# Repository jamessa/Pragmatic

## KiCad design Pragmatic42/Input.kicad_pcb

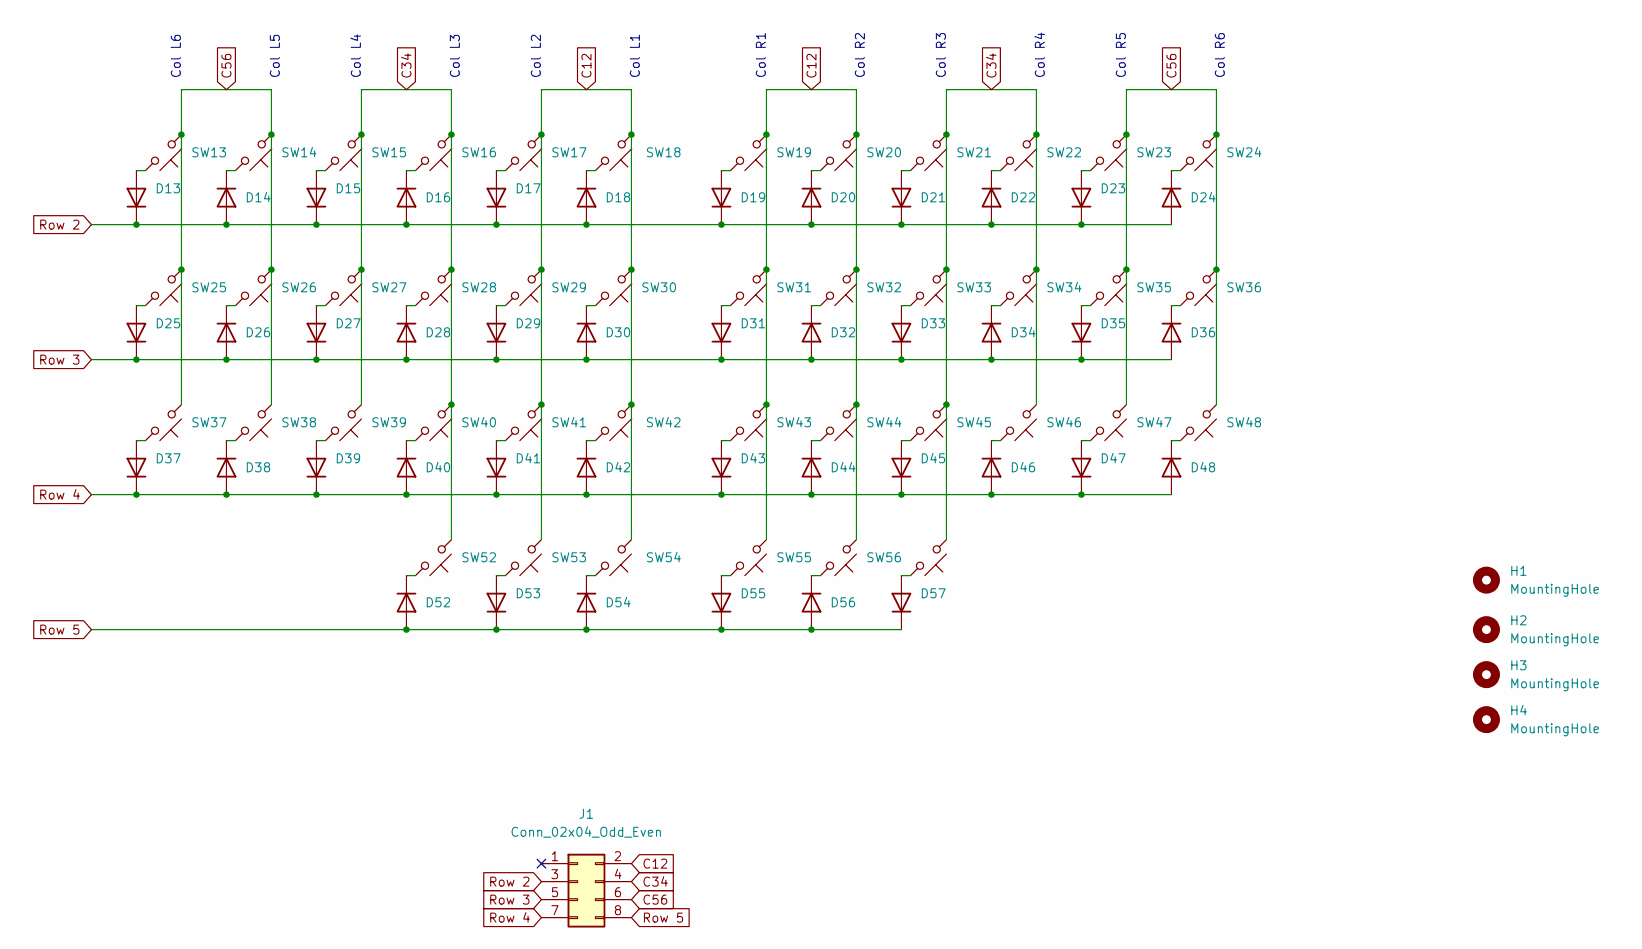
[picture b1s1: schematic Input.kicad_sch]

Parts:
D13, D14, D15, D16, D17, D18, D19, D20, D21, D22, D23, D24, D25, D26, D27, D28, D29, D30, D31, D32, D33, D34, D35, D36, D37, D38, D39, D40, D41, D42, D43, D44, D45, D46, D47, D48, D52, D53, D54, D55, D56, D57: 1N4448W; D3_SMD_v2
H1, H2, H3, H4: MountingHole; MountingHole_3.2mm_M3_DIN965
J1: Conn_02x04_Odd_Even; matrix_connector
SW13, SW14, SW15, SW16, SW17, SW18, SW25, SW26, SW27, SW28, SW29, SW30, SW37, SW38, SW39, SW40, SW41, SW42, SW52, SW53, SW54: SW_Push_45deg; ChocV1_Hotswap_reverse
SW19, SW20, SW21, SW22, SW23, SW24, SW31, SW32, SW33, SW34, SW35, SW36, SW43, SW44, SW45, SW46, SW47, SW48, SW55, SW56, SW57: SW_Push_45deg; ChocV1_Hotswap

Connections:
C12: J1.2, SW17.1, SW18.1, SW19.1, SW20.1, SW29.1, SW30.1, SW31.1, SW32.1, SW41.1, SW42.1, SW43.1, SW44.1, SW53.1, SW54.1, SW55.1, SW56.1
C34: J1.4, SW15.1, SW16.1, SW21.1, SW22.1, SW27.1, SW28.1, SW33.1, SW34.1, SW39.1, SW40.1, SW45.1, SW46.1, SW52.1, SW57.1
C56: J1.6, SW13.1, SW14.1, SW23.1, SW24.1, SW25.1, SW26.1, SW35.1, SW36.1, SW37.1, SW38.1, SW47.1, SW48.1
unnamed: D13.2 (A), SW13.2
unnamed: D14.1 (K), SW14.2
unnamed: D15.2 (A), SW15.2
unnamed: D16.1 (K), SW16.2
unnamed: D17.2 (A), SW17.2
unnamed: D18.1 (K), SW18.2
unnamed: D19.2 (A), SW19.2
unnamed: D20.1 (K), SW20.2
unnamed: D21.2 (A), SW21.2
unnamed: D22.1 (K), SW22.2
unnamed: D23.2 (A), SW23.2
unnamed: D24.1 (K), SW24.2
unnamed: D25.2 (A), SW25.2
unnamed: D26.1 (K), SW26.2
unnamed: D27.2 (A), SW27.2
unnamed: D28.1 (K), SW28.2
unnamed: D29.2 (A), SW29.2
unnamed: D30.1 (K), SW30.2
unnamed: D31.2 (A), SW31.2
unnamed: D32.1 (K), SW32.2
unnamed: D33.2 (A), SW33.2
unnamed: D34.1 (K), SW34.2
unnamed: D35.2 (A), SW35.2
unnamed: D36.1 (K), SW36.2
unnamed: D37.2 (A), SW37.2
unnamed: D38.1 (K), SW38.2
unnamed: D39.2 (A), SW39.2
unnamed: D40.1 (K), SW40.2
unnamed: D41.2 (A), SW41.2
unnamed: D42.1 (K), SW42.2
unnamed: D43.2 (A), SW43.2
unnamed: D44.1 (K), SW44.2
unnamed: D45.2 (A), SW45.2
unnamed: D46.1 (K), SW46.2
unnamed: D47.2 (A), SW47.2
unnamed: D48.1 (K), SW48.2
unnamed: D52.1 (K), SW52.2
unnamed: D53.2 (A), SW53.2
unnamed: D54.1 (K), SW54.2
unnamed: D55.2 (A), SW55.2
unnamed: D56.1 (K), SW56.2
unnamed: D57.2 (A), SW57.2
Row 2: D13.1 (K), D14.2 (A), D15.1 (K), D16.2 (A), D17.1 (K), D18.2 (A), D19.1 (K), D20.2 (A), D21.1 (K), D22.2 (A), D23.1 (K), D24.2 (A), J1.3
Row 3: D25.1 (K), D26.2 (A), D27.1 (K), D28.2 (A), D29.1 (K), D30.2 (A), D31.1 (K), D32.2 (A), D33.1 (K), D34.2 (A), D35.1 (K), D36.2 (A), J1.5
Row 4: D37.1 (K), D38.2 (A), D39.1 (K), D40.2 (A), D41.1 (K), D42.2 (A), D43.1 (K), D44.2 (A), D45.1 (K), D46.2 (A), D47.1 (K), D48.2 (A), J1.7
Row 5: D52.2 (A), D53.1 (K), D54.2 (A), D55.1 (K), D56.2 (A), D57.1 (K), J1.8

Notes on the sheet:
Col L4
Col R1
Col L1
Col R5
Col L6
Col R3
Col L3
Col R6
Col L5
Col R2
Col R4
Col L2

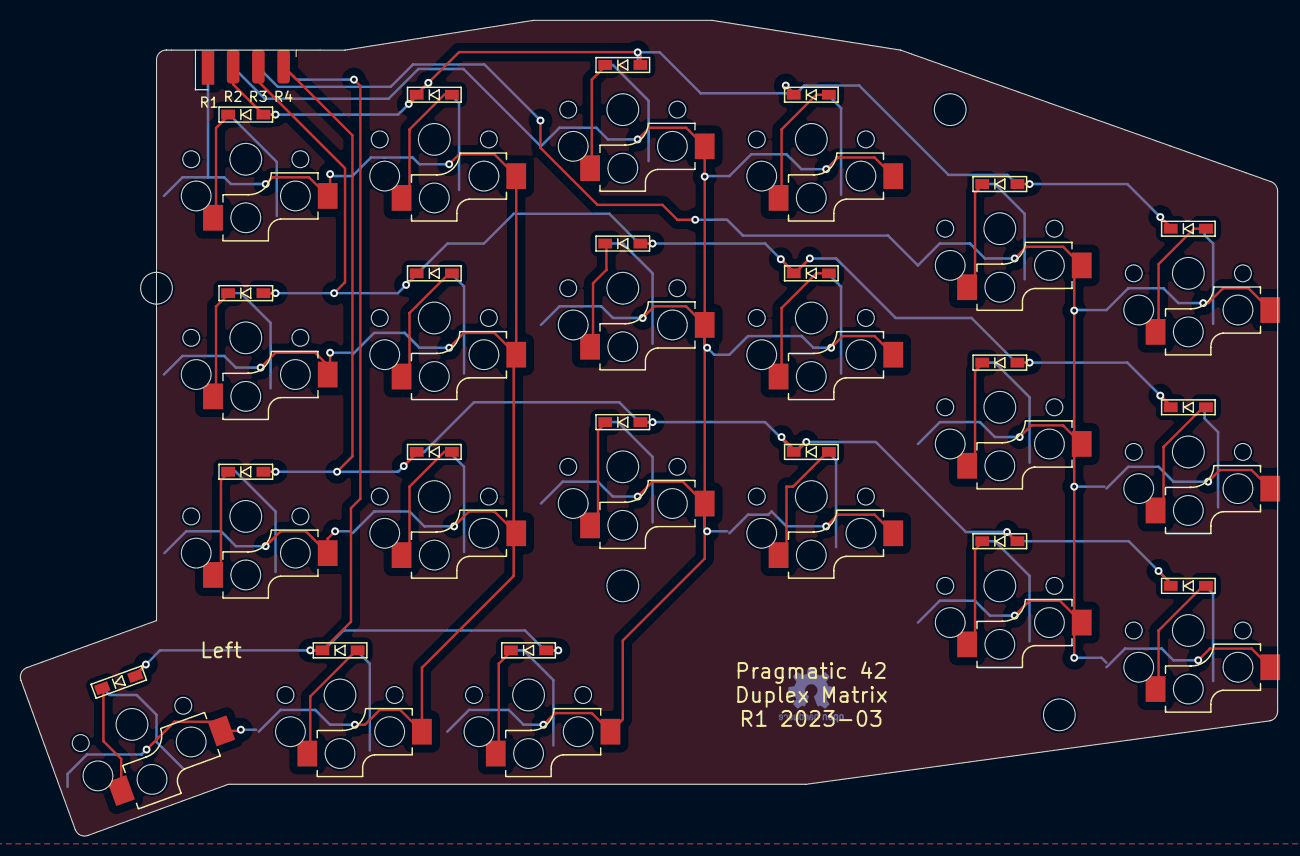
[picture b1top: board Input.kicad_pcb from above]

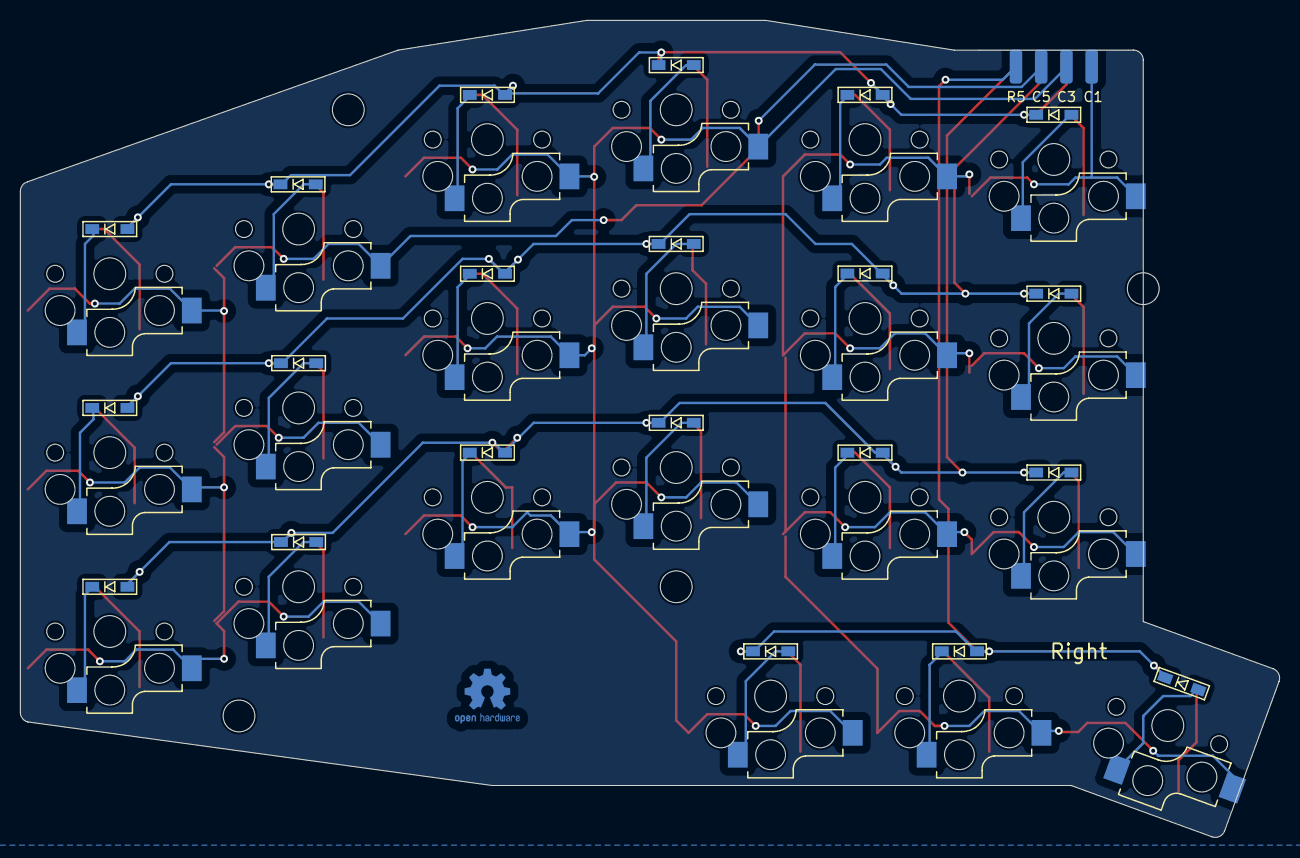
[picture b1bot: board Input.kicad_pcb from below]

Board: 2 copper layers, 126.7 x 82.2 mm, 89 parts (42 on the bottom side), 49 nets.

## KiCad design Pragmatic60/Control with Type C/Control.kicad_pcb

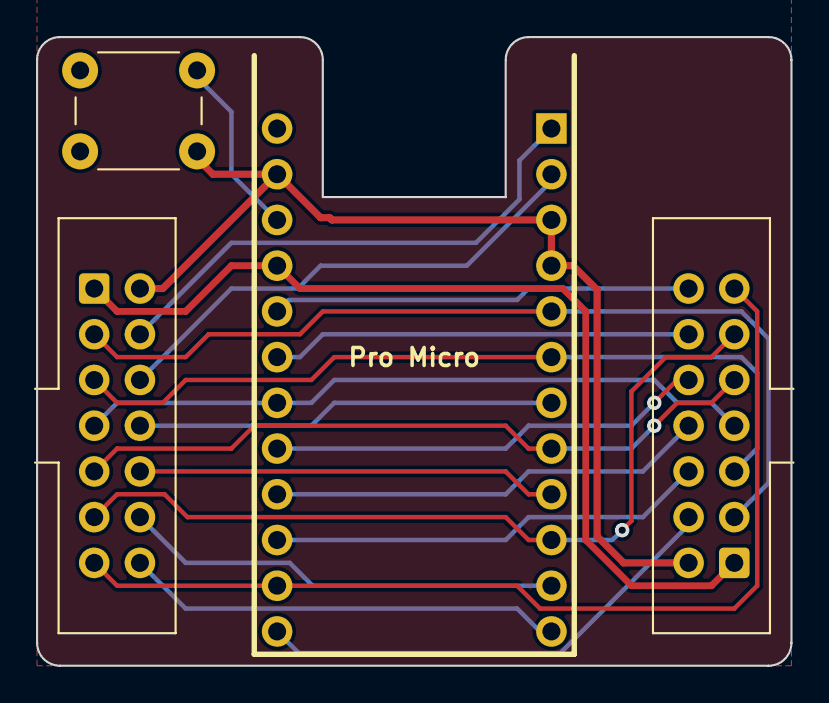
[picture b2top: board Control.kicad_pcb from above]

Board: 2 copper layers, 41.9 x 34.9 mm, 6 parts (1 on the bottom side), 21 nets.

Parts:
J1: L; IDC-Header_2x07_P2.54mm_Vertical
J2: R; IDC-Header_2x07_P2.54mm_Vertical
L1: JLC Legend
Logo1: OSHW-Symbol_6.7x6mm_Copper
SW1: SW_Push; SW_PUSH_6mm
U1: ProMicro; ProMicro Type C Reversed

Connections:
Col1: J1.4, U1.1 (TX0/PD3)
Col2: J1.6, U1.2 (RX1/PD2)
Col3: J1.8, U1.7 (4/PD4)
Col4: J1.10, U1.9 (6/PD7)
Col5: J1.12, U1.11 (8/PB4)
Col6: J1.14, U1.12 (9/PB5)
Col7: J2.4, U1.13 (10/PB6)
Col8: J2.6, U1.15 (14/PB3)
Col9: J2.8, U1.16 (15/PB1)
Col10: J2.10, U1.17 (A0/PF7)
Col11: J2.12, U1.19 (A2/PF5)
Col12: J2.14, U1.20 (A3/PF4)
GND: J1.2, J2.2, SW1.2, U1.3 (GND), U1.4 (GND), U1.23 (GND)
Reset: SW1.1, U1.22 (RST)
Row1: J1.3, J2.3, U1.5 (2/PD1)
Row2: J1.5, J2.5, U1.6 (3/PD0)
Row3: J1.7, J2.7, U1.18 (A1/PF6)
Row4: J1.9, J2.9, U1.8 (5/PC6)
Row5: J1.11, J2.11, U1.10 (7/PE6)
Row6: J1.13, J2.13, U1.14 (16/PB2)
VCC: J1.1, J2.1, U1.21 (VCC)

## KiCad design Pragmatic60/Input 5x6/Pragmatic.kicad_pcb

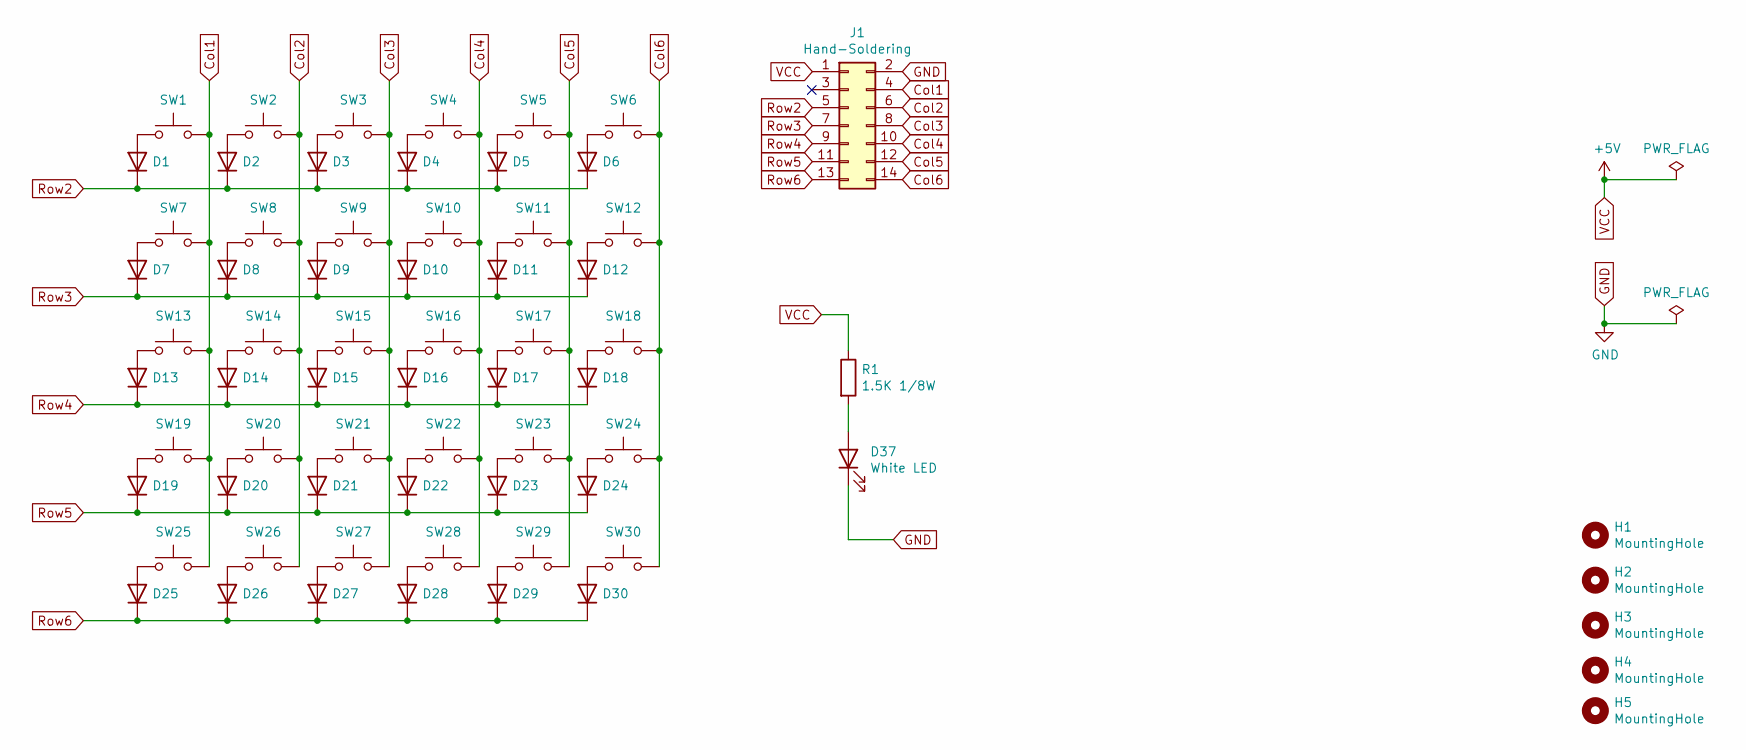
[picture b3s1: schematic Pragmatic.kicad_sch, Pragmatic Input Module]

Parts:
D1, D2, D3, D4, D5, D6, D7, D8, D9, D10, D11, D12, D13, D14, D15, D16, D17, D18, D19, D20, D21, D22, D23, D24, D25, D26, D27, D28, D29, D30: 1N4148; D3_SMD_v2; LCSC C81598
D37: White LED; LED_0805_2012Metric_Pad1.15x1.40mm_HandSolder; LCSC C434434
H1, H2, H3, H4, H5: MountingHole; MountingHole_2.5mm
J1: Hand-Soldering; IDC-Header_2x07_P2.54mm_Vertical; LCSC C3406
R1: 1.5K 1/8W; R_0805_2012Metric_Pad1.20x1.40mm_HandSolder; LCSC C4310
SW1, SW2, SW3, SW4, SW5, SW6, SW7, SW8, SW9, SW10, SW11, SW12, SW13, SW14, SW15, SW16, SW17, SW18, SW19, SW20, SW21, SW22, SW23, SW24, SW25, SW26, SW27, SW28, SW29, SW30: SW_Push; MX_Hotswap_MX_Choc_Solder; LCSC C2803348

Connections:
Col1: J1.4, SW1.2, SW7.2, SW13.2, SW19.2, SW25.2
Col2: J1.6, SW2.2, SW8.2, SW14.2, SW20.2, SW26.2
Col3: J1.8, SW3.2, SW9.2, SW15.2, SW21.2, SW27.2
Col4: J1.10, SW4.2, SW10.2, SW16.2, SW22.2, SW28.2
Col5: J1.12, SW5.2, SW11.2, SW17.2, SW23.2, SW29.2
Col6: J1.14, SW6.2, SW12.2, SW18.2, SW24.2, SW30.2
GND: D37.1 (K), J1.2
unnamed: D1.2 (A), SW1.1
unnamed: D2.2 (A), SW2.1
unnamed: D3.2 (A), SW3.1
unnamed: D4.2 (A), SW4.1
unnamed: D5.2 (A), SW5.1
unnamed: D6.2 (A), SW6.1
unnamed: D7.2 (A), SW7.1
unnamed: D8.2 (A), SW8.1
unnamed: D9.2 (A), SW9.1
unnamed: D10.2 (A), SW10.1
unnamed: D11.2 (A), SW11.1
unnamed: D12.2 (A), SW12.1
unnamed: D13.2 (A), SW13.1
unnamed: D14.2 (A), SW14.1
unnamed: D15.2 (A), SW15.1
unnamed: D16.2 (A), SW16.1
unnamed: D17.2 (A), SW17.1
unnamed: D18.2 (A), SW18.1
unnamed: D19.2 (A), SW19.1
unnamed: D20.2 (A), SW20.1
unnamed: D21.2 (A), SW21.1
unnamed: D22.2 (A), SW22.1
unnamed: D23.2 (A), SW23.1
unnamed: D24.2 (A), SW24.1
unnamed: D25.2 (A), SW25.1
unnamed: D26.2 (A), SW26.1
unnamed: D27.2 (A), SW27.1
unnamed: D28.2 (A), SW28.1
unnamed: D29.2 (A), SW29.1
unnamed: D30.2 (A), SW30.1
unnamed: D37.2 (A), R1.2
Row2: D1.1 (K), D2.1 (K), D3.1 (K), D4.1 (K), D5.1 (K), D6.1 (K), J1.5
Row3: D7.1 (K), D8.1 (K), D9.1 (K), D10.1 (K), D11.1 (K), D12.1 (K), J1.7
Row4: D13.1 (K), D14.1 (K), D15.1 (K), D16.1 (K), D17.1 (K), D18.1 (K), J1.9
Row5: D19.1 (K), D20.1 (K), D21.1 (K), D22.1 (K), D23.1 (K), D24.1 (K), J1.11
Row6: D25.1 (K), D26.1 (K), D27.1 (K), D28.1 (K), D29.1 (K), D30.1 (K), J1.13
VCC: J1.1, R1.1

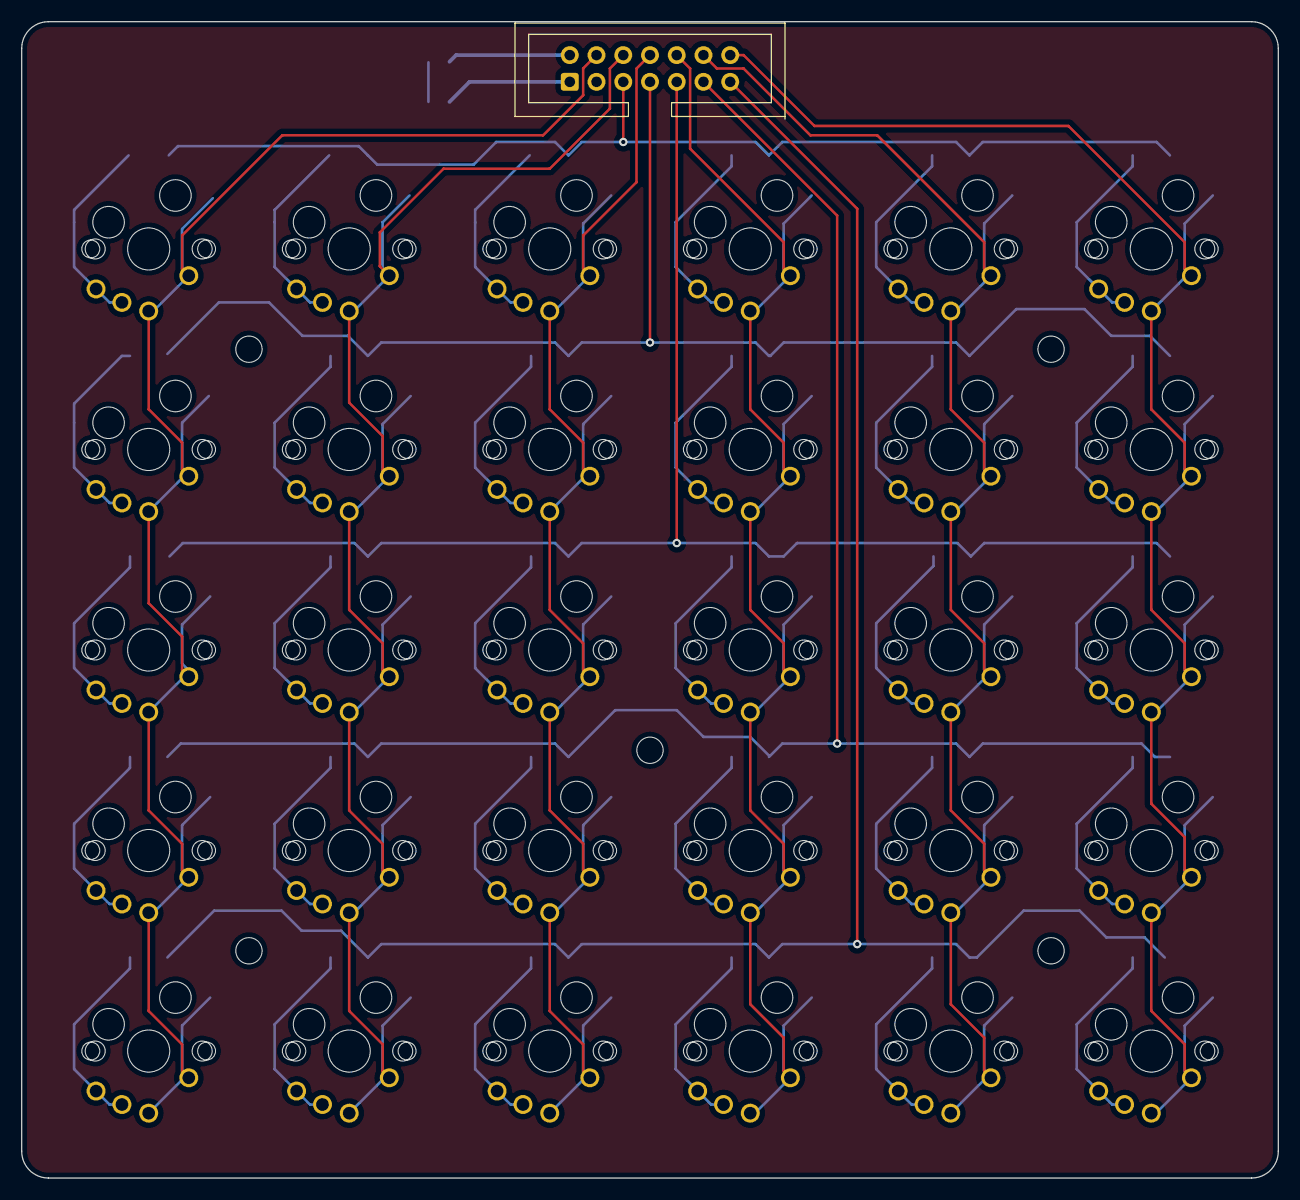
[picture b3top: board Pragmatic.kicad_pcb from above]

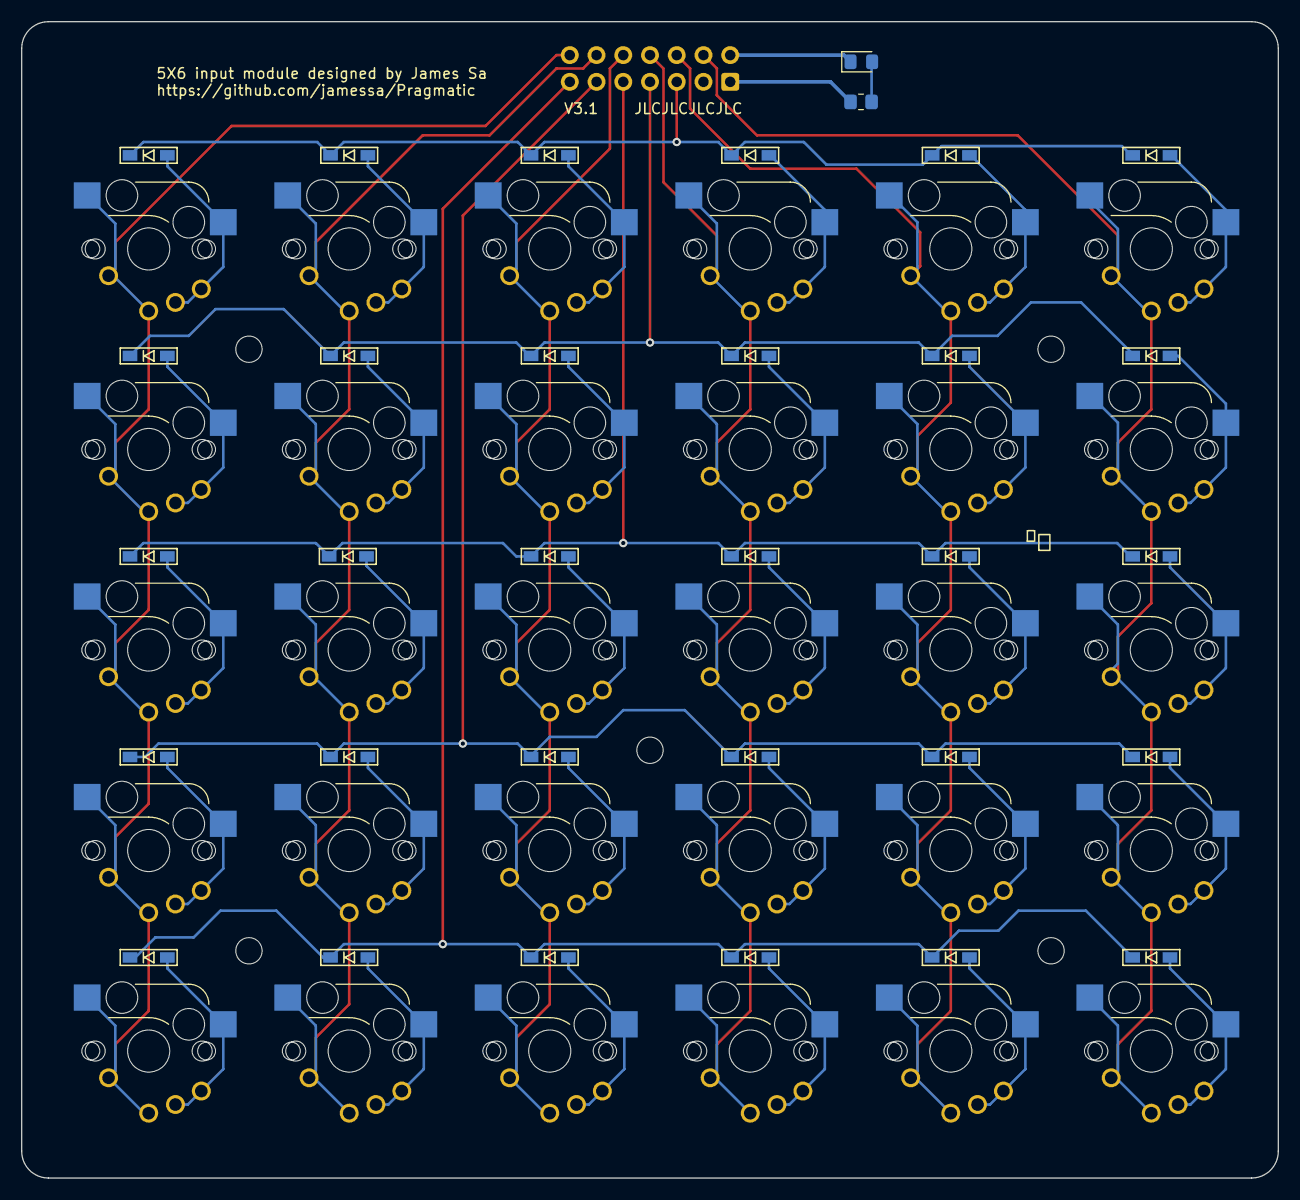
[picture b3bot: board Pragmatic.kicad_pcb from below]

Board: 2 copper layers, 119.4 x 109.9 mm, 68 parts (62 on the bottom side), 44 nets.
